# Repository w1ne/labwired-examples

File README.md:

# LabWired Examples

Real firmware, inspectable circuit diagrams, reproducible simulator oracles, and (when relevant) parametric mechanical models in [KernelCAD](https://kernelcad.com/).

This repository is for runnable hardware verification stories, **not concept art or untested AI-generated designs**. Each example states which behavior was verified, where the simulator approximates hardware, and what remains missing.

## Catalog

| Example | Firmware and electronics | Mechanics | Evidence |
| --- | --- | --- | --- |
| [Game Boy-compatible handheld](examples/gaming/gameboy-handheld/) | STM32F411 C firmware runs Peanut-GB and an original ROM; ILI9341 and eight controls | Shared carrier/case interfaces, attached exact-source KiCad board, 59 CAD parts and 58 fixed mates | Saved-project MCU verification, host ROM behavior, browser input, hosted native PCB DRC/attachment and static CAD checks; no physical hardware |
| [HeyPCB imported-board acceptance sample](examples/pcb/heypcb-import-acceptance/) | Seven pinned KiCad PCB files and model-gap evidence; no full-board pass | No mechanical model | Source blobs verified; seven imports reported in unmerged PR #2934; none completely simulated |
| [Industrial BLDC fault verification](examples/industrial/bldc-fault-verification/) | STM32L476 compiled C, 24 V motor plant, three digital fault flags, inverter shutdown | No mechanical model in this example | Normal spin-up and 3 fault scenarios model-verified; ideal MCU supply, no physical bench |
| [Quadrotor co-design](examples/robotics/quadrotor-bldc/) | Four STM32L476 C channels; separate native six-layer ESC with zero configured ERC/DRC findings | 38-part saved KernelCAD revision 5 with populated native ESC and FC; four rotor joints | Candidate browser: 360 exact motor/CAD observations, isolated fault, pause and reset. Actual board simulation and flight remain open. |

## Featured video

[Watch the 75-second quadrotor co-design engineering preview](examples/robotics/quadrotor-bldc/media/quadrotor-engineering-preview.mp4): editable CAD, exploded assembly, native schematic/PCB, four live motor channels, a selected-channel fault, pause and reset. This is actual application footage of a candidate STM32 propulsion bench. The physical OpenESC board and aircraft flight are not simulated by that bench.

## Run

Open an example directory. It contains firmware source, the exact LabWired circuit JSON, observed test evidence, editable KernelCAD source when appropriate, and screenshots recorded from the actual tools. Each example links to a runnable LabWired project and a versioned KernelCAD design.

For an introduction to firmware-aware circuit simulation, use the [LabWired circuit simulator guide](https://labwired.com/circuit-simulator/). It links to a GPIO-to-RC oscilloscope demonstration and explains the different browser linear-circuit and native ngspice capabilities. The quadrotor example above is a separate motor-control verification.

## Contribution standard

New examples need catalog-validated connectivity, compilable firmware, an explicit test oracle, and precise model limits. For mechanical projects, keep editable KernelCAD source and verified joints. See [CONTRIBUTING.md](CONTRIBUTING.md).

**Core simulator and firmware-model changes belong in [w1ne/labwired-core](https://github.com/w1ne/labwired-core).** This repository stores reproducible consumers of that engine, not copies of the engine.

## Licensing

Example source and scripts are MIT licensed. Individual CAD assets may carry CC0-1.0 declarations in their metadata. Manufacturer names (including ODrive) are descriptive and do not imply endorsement, compatibility or use of proprietary software.

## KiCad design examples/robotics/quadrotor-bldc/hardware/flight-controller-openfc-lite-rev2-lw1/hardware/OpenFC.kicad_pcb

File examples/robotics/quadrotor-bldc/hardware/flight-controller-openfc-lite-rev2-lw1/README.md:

# OpenFC-Lite revision 2-LW1 — review candidate

This is an editable, separately versioned repair of the pinned OpenFC-Lite
revision 2. It is **not a manufacturing release or a native firmware acceptance**.
The original submodule remains unchanged at
`def4ab29a5af430551aa15756b747e9ad6d4c480`.

The candidate passes the configured KiCad 10.0.8 physical DRC with **zero
errors and zero unconnected items**. One original physical omission remains:
Card1 DAT1 pad 8 has no PCB copper. Its parity warning is retained. ERC has
zero active errors after one exact, source-backed exclusion for the unused
LP5912 PG pin connected to ground. All design rules and ERC severities are
unchanged.

[Editable PCB](hardware/OpenFC.kicad_pcb) ·
[Editable schematic](hardware/OpenFC.kicad_sch) ·
[Seven-sheet review PDF](validation/schematic-rev2-lw1.pdf) ·
[Immutable source and result manifest](source-and-validation.json)

## Changes

| Item | Change and reason | Preserved contract |
| --- | --- | --- |
| U9 BMI270 | Disconnect ASDx/ASCx, physical pads 2/3, from GND in the schematic and PCB. Remove the single GND via that touched both pads and refill the zones. | The two existing copper pads remain; all other physical net assignments are unchanged. |
| U10 SN74LVC1G3157DTBR | Use the separately named TI DTB0006A Rev C land-pattern example, extracted from TI's mask and paste vectors. Reroute the six local connections and move C38 by 0.30 mm to accommodate that geometry. | Body pose, physical pin identities, source 3D model, existing net names, minimum clearance and via rules remain. |
| Original hole-clearance errors | Move J15, J28 and J54 by the recorded small offsets and update their same-net leads. | Pad shapes, contact identities and board outline remain. |
| Four omitted pads | Restore USB1 A8/B8 and LP5912 U7/U15 pad 2 from their existing footprint-library templates. Move one GND via by 0.1393 mm to clear USB1 A8. | The new pads are isolated NC contacts. No signal or supply is added. |
| Pin and part annotations | Correct U2 GPIO11 to bidirectional, U15 OUT to power output, U7 physical PG3/GND5 identity, Q1/Q2 manufacturer to ALLPOWER, and the U15 500 mA heading. Copy missing PCB MPN/manufacturer fields from the original schematic. | No passive component is retyped as a power source. Part numbers and existing connections remain. |
| ERC intent | Add seven PWR_FLAG symbols only at reviewed external entries or regulator/inductor/diode source paths. Add one exact PG-to-GND exclusion with its TI reference. | The importer ignores these annotations as electrical sources. The unpowered circuit still refuses the actual battery-input net. |
| Revision identity | Date all seven copied sheets 2026-11-12 and label them 2-LW1. | Upstream revision 2 remains available unchanged. |

The LP5912 NC restorations use the existing source/KiCad pattern: 0.375 ×
0.4 mm pads at x = ±0.8875 mm. TI's separate example uses different dimensions.
This repair does not claim that the source pattern is TI's land-pattern
example. U10's new footprint is explicitly a TI example extraction and is
recorded separately.

## Manufacturer evidence

Bosch's [BMI270 datasheet BST-BMI270-DS000-08](https://www.bosch-sensortec.com/media/boschsensortec/downloads/datasheets/bst-bmi270-ds000.pdf),
page 135, states for the auxiliary pins: **“Do not connect to GND.”**
The original board assigned both pads to GND and one GND via physically
contacted both. The final read-only KiCad shape test checks each restored
or corrected NC pad against all pads, tracks, vias and filled copper on its
copper layer. All six tested pads have zero contacts.

TI's [SN74LVC1G3157 datasheet SCES424O](https://www.ti.com/lit/ds/symlink/sn74lvc1g3157.pdf),
pages 54–55, provides the DTB0006A example mask and paste geometry used for
U10. The extraction retains the polygon contours, rounded corners, 0.1 mm
primitive stroke, separate paste apertures and 0.01 mm anchors. This provides
a nominal 0.10 mm copper gap against the existing 0.09 mm rule. The footprint
is not approximated by pad rectangles.

TI's [LP5912 datasheet SNVSA77D](https://www.ti.com/lit/ds/symlink/lp5912.pdf),
section 6, identifies PG as pad 3 and GND as pad 5. Section 8.3.6 permits an
unused PG pin to be grounded or left floating. The source connects both
pads to GND. The repaired symbol has the correct identity and open-collector
annotation. KiCad's generic rule still flags that explicitly permitted
connection against the GND PWR_FLAG. Only that marker's two pin UUIDs and
sheet paths are excluded; the reason and PDF hash are stored in the project
and [exclusion receipt](validation/documented-pg-erc-exclusion.json).

PDF hashes, source-library hashes and exact geometry changes are preserved
in the manifest and per-change receipts. These checks do not qualify solder
processes, current capacity, signal integrity, thermal behavior or production
yield.

## Observed checks

| KiCad 10.0.8 check | Pinned source | Revision 2-LW1 |
| --- | ---: | ---: |
| Physical DRC errors | 5: four hole-clearance, one copper-clearance | 0 |
| Physical DRC warnings | 11 | 5 |
| Unconnected PCB items | 0 | 0 |
| Schematic/PCB parity warnings | 17 | 1: Card1 DAT1 pad 8 omitted |
| Active ERC errors | 9: eight supply declarations, one input-driver declaration | 0 |
| ERC warnings | 182 | 178 |
| Exact documented ERC exclusions | 0 | 1: unused U7 PG3 grounded |

The five final physical warnings are four preserved source/library footprint
mismatches and the original non-mirrored `B = SIGNAL` annotation outside the
board. The 178 ERC warnings are retained; this repair does not reclassify
unknown pin roles or change the global pin-compatibility matrix to clear them.
The installed environment substitutes DejaVu for the unavailable Tokyo font.

The final board has **164 footprints and 583 pad objects**, up from 579 pad
objects. Its 19 zones were refilled with the original rules. All 445
schematic electrical endpoints remain. Only U9 pads 2/3 change their net
assignment. The six U10 pads each retain an actual same-net track contact.
See [native PCB proof](validation/final-pcb-connectivity-proof.json) and
[schematic endpoint proof](validation/schematic-connectivity-proof.json).

The actual app importer produces the same 160-part, 82-net graph before and
after the ERC flags and symbol annotations. Diagram, resolved nets, mapping,
compiler result and lowerer result are identical. The source-free import
still fails with `PWR_RAIL_UNDRIVEN` on `net@C22:1`, which contains the real
P1/J29 battery input and U6/U16 input rails. This proves that ERC annotations
cannot create an ideal battery or regulator supply. It does **not** prove a
powered native boot or qualify the RP2354B internal buck regulator.

## Remaining physical omission

Card1 DAT1 pad 8 is present in the schematic as an unused contact and in the
source footprint library, but absent from the native PCB. The exact 0.7 ×
1.6 mm library pad overlaps three existing power vias and approaches a USB
D− via and a GND via. A bounded same-net reroute was tested; it intersected
adjacent USB/DVDD/IOVDD escape routing. Those trial power and signal edits
were completely reverted. The accepted board retains the original omission
and its parity warning. No pad was shrunk and no rule or parity exclusion
was added to conceal it.

The rejected-candidate DRC reports remain in `validation/` as evidence of this
limit. They are **not** the final board reports. A broader connector/power/USB
escape redesign and its signal-integrity review remain required before
calling the copied board complete.

The existing populated KernelCAD revision 4 uses earlier board geometry.
Its fit receipt cannot qualify the moved components or changed copper in
2-LW1. This candidate also does not establish native sensor startup,
Betaflight arming, ESC operation, flight control or physical power-on.

## Model availability at review

The [model inventory](validation/model-resolution-inventory.json) records
107 enabled source model references. Eleven references resolve to ten cached
upstream files; each file matches its exact Git blob at the pinned upstream
commit. The environment lacks 17 standard KiCad STEP files used by 96 other
references. The 57 footprints without models are 53 solder contacts and four
testpoints. The committed hardware refers to the original pinned model
library through relative links; initialize that submodule to resolve them.

All source model paths, offsets and rotations remain unchanged. The native
inductor entries reference generic Murata/Changjiang package models. Their
presence does not establish manufacturer-specific dimensions. Root assembly
work must resolve and inspect the missing models and verify the newly moved
parts before claiming a populated FC fit.

## Reproduce

1. Initialize the original pinned source and its libraries:
   `git submodule update --init --recursive examples/robotics/quadrotor-bldc/hardware/flight-controller-openfc-lite`.
   The two relative library/model links in this copy refer to that source.
2. Use KiCad 10.0.8 with its standard symbol/footprint libraries and the project
   tables. Run `validation/run_native_checks.sh` with an output directory.
   The script does not edit or refill the board; it audits the committed fill.
3. Run the read-only `validation/verify_pcb.py` with KiCad's `pcbnew` Python
   environment, the pinned original board, the copied board, and an output
   receipt path. It compares pad identities, nets, geometry changes and direct
   NC copper contacts, and verifies the single allowed project-metadata delta.
4. To repeat app import checks, set `LABWIRED_APP_ROOT` to the reviewed app
   checkout listed in the manifest. Run `node --import tsx
   validation/audit_import.mjs INPUT.net OUTPUT.json` from that app checkout.
   Compare the recorded before-annotation and final netlists. The exact app
   source and generated metadata are required; an older released catalog
   cannot reproduce this onboarding result.
5. Run the repository's `python3 -m unittest discover -s scripts -p
   'test_*.py' -v` integrity suite. These tests verify archived source/evidence
   consistency; they do not substitute for KiCad or a physical test.

## Source and licence

The copied hardware derives from
[OpenDrone-hw/OpenFC-Lite](https://github.com/OpenDrone-hw/OpenFC-Lite/tree/def4ab29a5af430551aa15756b747e9ad6d4c480).
It remains under the upstream **CERN-OHL-S-2.0** licence, reproduced in
[LICENSE](LICENSE). The enclosing examples repository's general MIT notice
does not replace that hardware licence. This directory is a LabWired repair
candidate, not an upstream release or manufacturer endorsement. The editable
source, explicit changes and verification records accompany the copy.

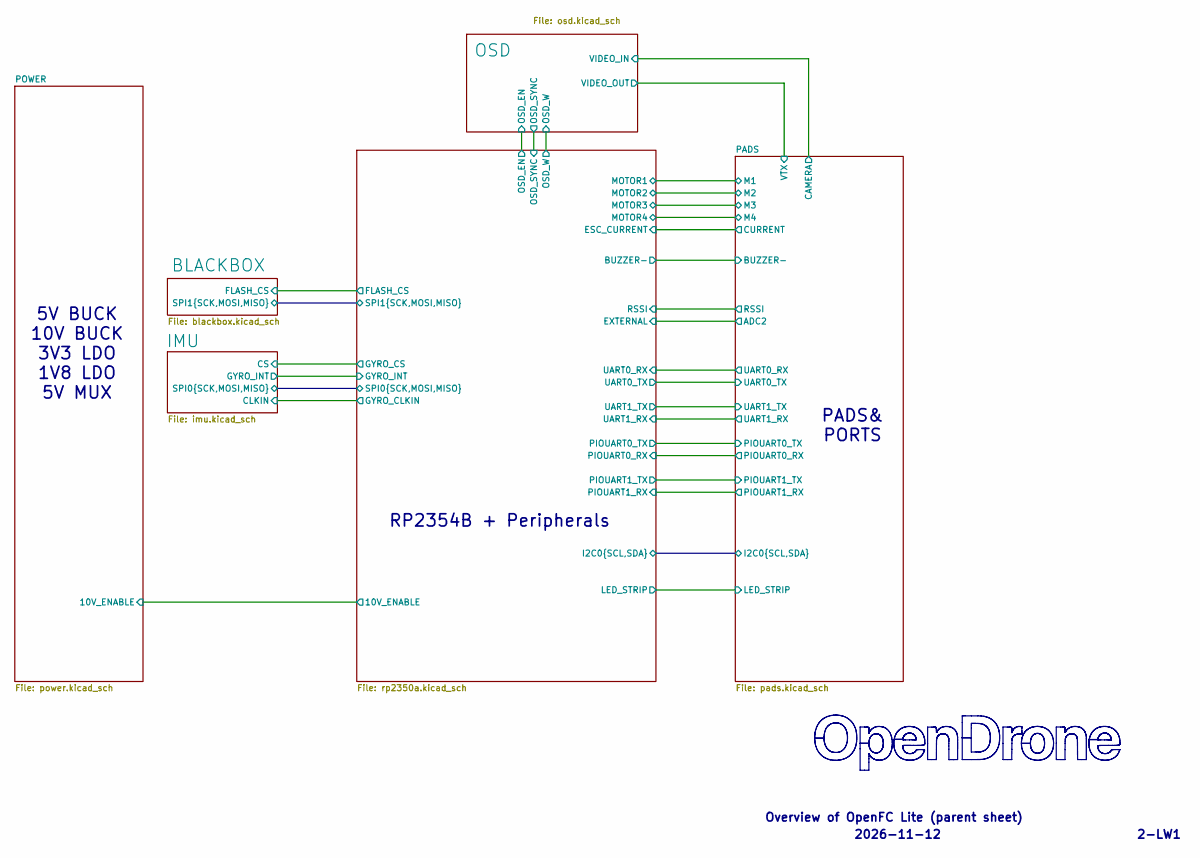
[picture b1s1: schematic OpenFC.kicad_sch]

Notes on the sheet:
Overview of OpenFC Lite (parent sheet)
5V BUCK 10V BUCK 3V3 LDO 1V8 LDO 5V MUX
2-LW1
2026-11-12
RP2354B + Peripherals
PADS& PORTS

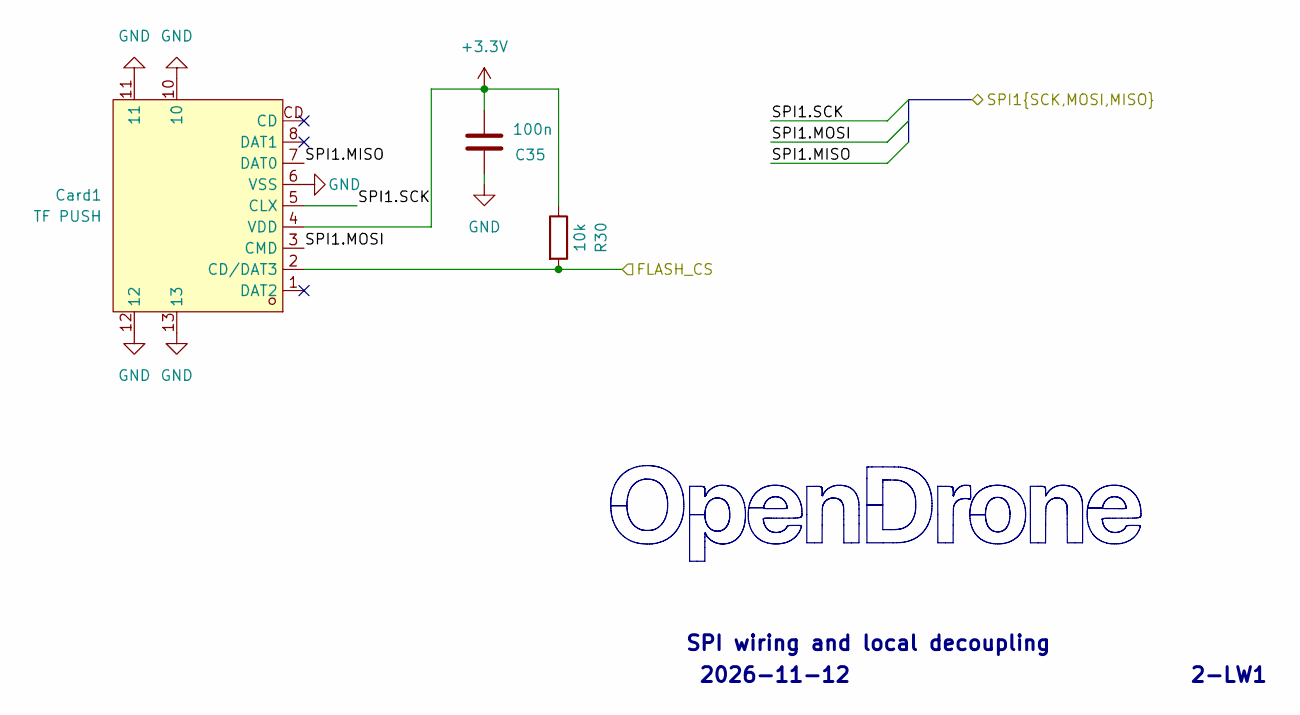
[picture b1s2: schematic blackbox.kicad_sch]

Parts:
C35: 100n; C_0201_0603Metric; MPN GRM033R61E104KE14D; LCSC C76939
Card1: TF PUSH; TF-SMD_TF-PUSH; MPN TF PUSH; LCSC C393941
R30: 10k; R_0201_0603Metric; MPN RC0201FR-0710KL; LCSC C106225

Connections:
+3.3V: C35.1, Card1.4 (VDD), R30.1; also elsewhere on the board
/BLACKBOX/FLASH_CS: Card1.2 (CD/DAT3), R30.2; also elsewhere on the board
/BLACKBOX/SPI1.MISO: Card1.7 (DAT0); also elsewhere on the board
/BLACKBOX/SPI1.MOSI: Card1.3 (CMD); also elsewhere on the board
/BLACKBOX/SPI1.SCK: Card1.5 (CLX); also elsewhere on the board
GND: C35.2, Card1.6 (VSS), Card1.10, Card1.11, Card1.12, Card1.13; also elsewhere on the board

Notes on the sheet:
SPI wiring and local decoupling
2026-11-12
2-LW1

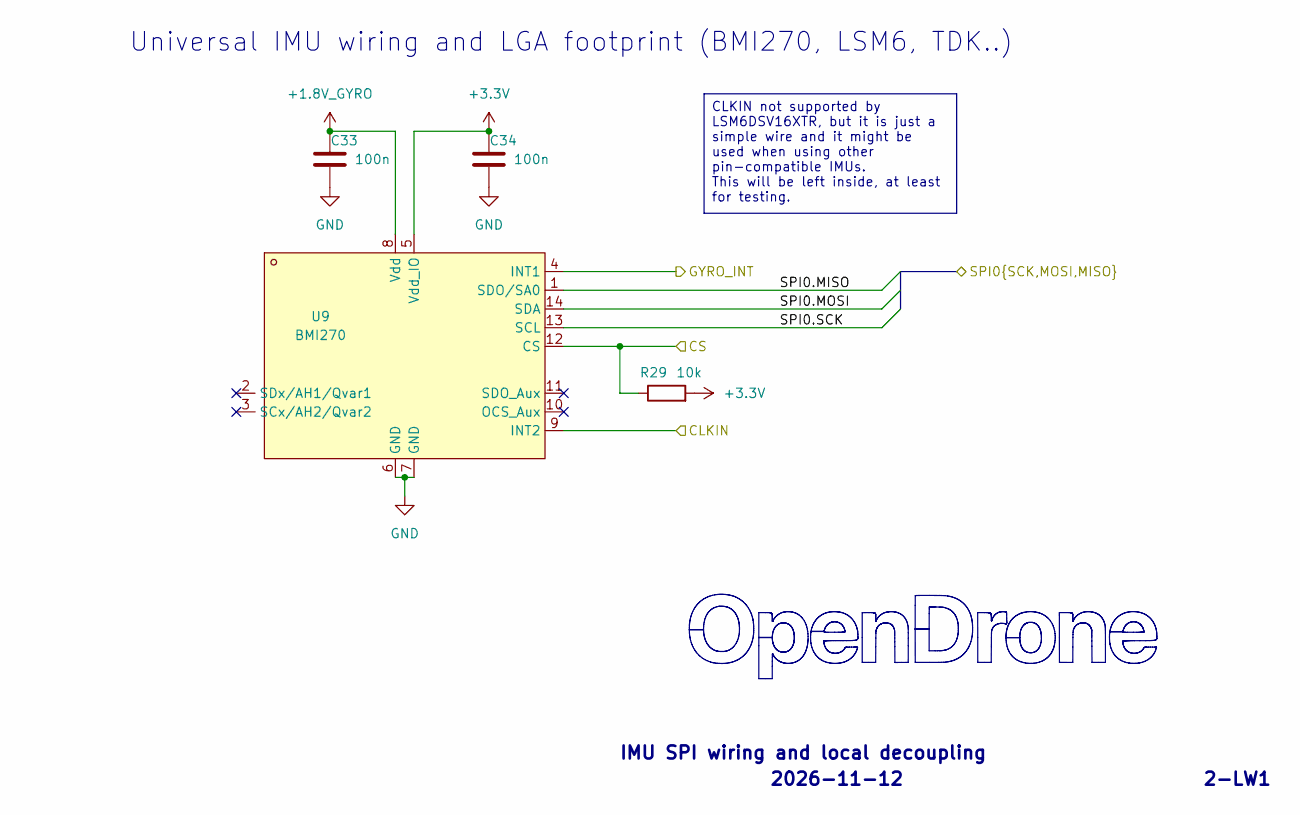
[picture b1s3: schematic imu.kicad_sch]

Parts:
C33, C34: 100n; C_0201_0603Metric; MPN GRM033R61E104KE14D; LCSC C76939
R29: 10k; R_0201_0603Metric; MPN RC0201FR-0710KL; LCSC C106225
U9: BMI270; LGA-14_L3.0-W2.5-P0.50-BR; MPN BMI270; LCSC C2836813

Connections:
+1.8V_GYRO: C33.1, U9.8 (Vdd); also elsewhere on the board
+3.3V: C34.1, R29.2, U9.5 (Vdd_IO); also elsewhere on the board
/IMU/CLKIN: U9.9 (INT2); also elsewhere on the board
/IMU/CS: R29.1, U9.12 (CS); also elsewhere on the board
/IMU/GYRO_INT: U9.4 (INT1); also elsewhere on the board
/IMU/SPI0.MISO: U9.1 (SDO/SA0); also elsewhere on the board
/IMU/SPI0.MOSI: U9.14 (SDA); also elsewhere on the board
/IMU/SPI0.SCK: U9.13 (SCL); also elsewhere on the board
GND: C33.2, C34.2, U9.6 (GND), U9.7 (GND); also elsewhere on the board

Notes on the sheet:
2-LW1
2026-11-12
IMU SPI wiring and local decoupling
Universal IMU wiring and LGA footprint (BMI270, LSM6, TDK..)
CLKIN not supported by LSM6DSV16XTR, but it is just a simple wire and it might be used when using other pin-compatible IMUs. This will be left inside, at least for testing.

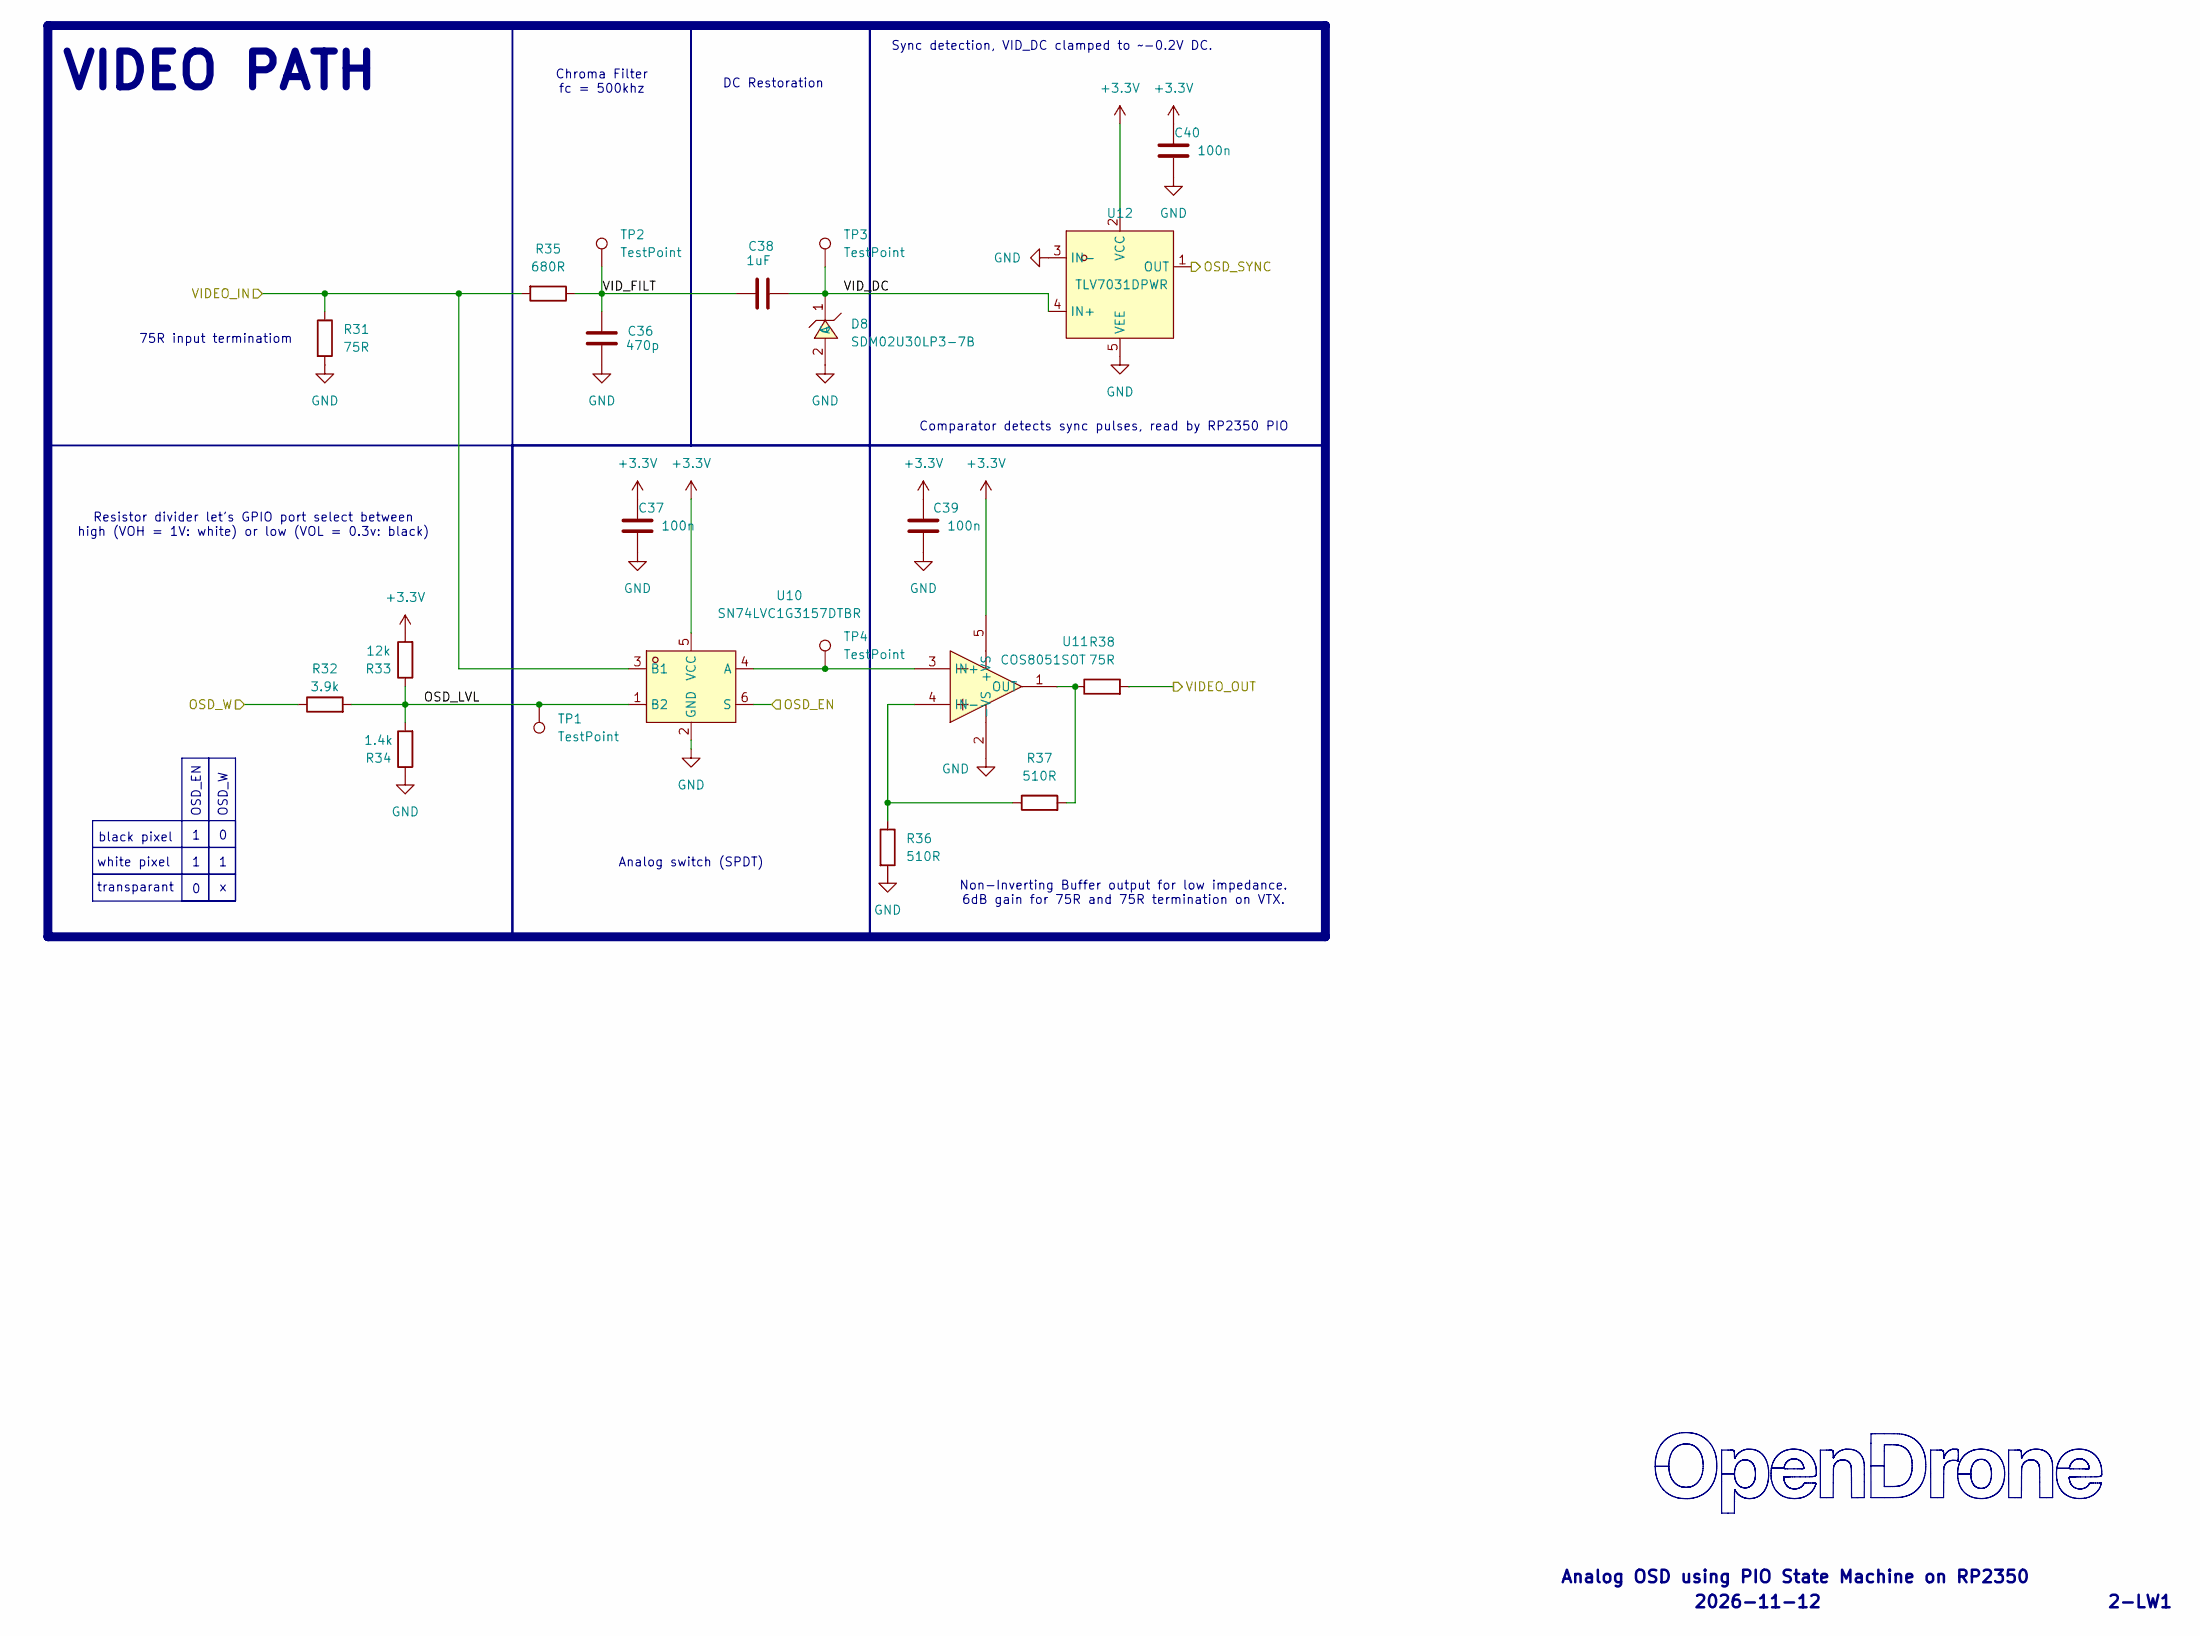
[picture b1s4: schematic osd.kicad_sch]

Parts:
C36: 470p; C_0201_0603Metric; MPN CC0201JRX7R9BB471; LCSC C526944
C37, C39, C40: 100n; C_0201_0603Metric; MPN GRM033R60J104KE19D; LCSC C76928
C38: 1uF; C_0402_1005Metric; MPN CL05A105KA5NQNC; LCSC C52923
D8: SDM02U30LP3-7B; X3-DFN0603-2_L0.6-W0.3-RD; MPN SDM02U30LP3-7B; LCSC C151629
R31, R38: 75R; R_0201_0603Metric; MPN RC0201FR-0775RL; LCSC C274878
R32: 3.9k; R_0201_0603Metric; MPN RC0201FR-073K9L; LCSC C273280
R33: 12k; R_0201_0603Metric; MPN 0201WMF1202TEE; LCSC C270363
R34: 1.4k; R_0201_0603Metric; MPN 0201WMF1401TEE; LCSC C423739
R35: 680R; R_0201_0603Metric; MPN 0201WMF6800TEE; LCSC C473509
R36, R37: 510R; R_0201_0603Metric; MPN RC0201FR-07510RL; LCSC C57784
TP1, TP2, TP3, TP4: TestPoint; TestPoint_Pad_D1.5mm
U10: SN74LVC1G3157DTBR; TI_DTB0006A_RevC_SMD; MPN SN74LVC1G3157DTBR; LCSC C2673087
U11: COS8051SOT; SOT-23-5_L3.0-W1.7-P0.95-LS2.8-BR; MPN COS8051SOT; LCSC C7463385
U12: TLV7031DPWR; X2SON-4_L0.8-W0.8-P0.48-TL-A; MPN TLV7031DPWR; LCSC C2876045

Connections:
+3.3V: C37.1, C39.1, C40.1, R33.2, U10.5 (VCC), U11.5 (+VS), U12.2 (VCC); also elsewhere on the board
/OSD/OSD_EN: U10.6 (S); also elsewhere on the board
/OSD/OSD_LVL: R32.2, R33.1, R34.2, TP1.1 (1_1), U10.1 (B2)
/OSD/OSD_SYNC: U12.1 (OUT); also elsewhere on the board
/OSD/OSD_W: R32.1; also elsewhere on the board
/OSD/VIDEO_IN: R31.1, R35.2, U10.3 (B1); also elsewhere on the board
/OSD/VIDEO_OUT: R38.2; also elsewhere on the board
/OSD/VID_DC: C38.2, D8.1 (C), TP3.1 (1_1), U12.4 (IN+)
/OSD/VID_FILT: C36.1, C38.1, R35.1, TP2.1 (1_1)
GND: C36.2, C37.2, C39.2, C40.2, D8.2 (A), R31.2, R34.1, R36.2, U10.2 (GND), U11.2 (-VS), U12.3 (IN-), U12.5 (VEE); also elsewhere on the board
unnamed: TP4.1 (1_1), U10.4 (A), U11.3 (IN+)
unnamed: R36.1, R37.1, U11.4 (IN-)
unnamed: R37.2, R38.1, U11.1 (OUT)

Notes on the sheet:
black pixel
Comparator detects sync pulses, read by RP2350 PIO
2026-11-12
Analog OSD using PIO State Machine on RP2350
Sync detection, VID_DC clamped to ~-0.2V DC.
Non-Inverting Buffer output for low impedance. 6dB gain for 75R and 75R termination on VTX.
2-LW1
white pixel
75R input terminatiom
OSD_W
Chroma Filter fc = 500khz
VIDEO PATH
Analog switch (SPDT)
OSD_EN
transparant
DC Restoration
Resistor divider let's GPIO port select between high (VOH = 1V: white) or low (VOL = 0.3v: black)

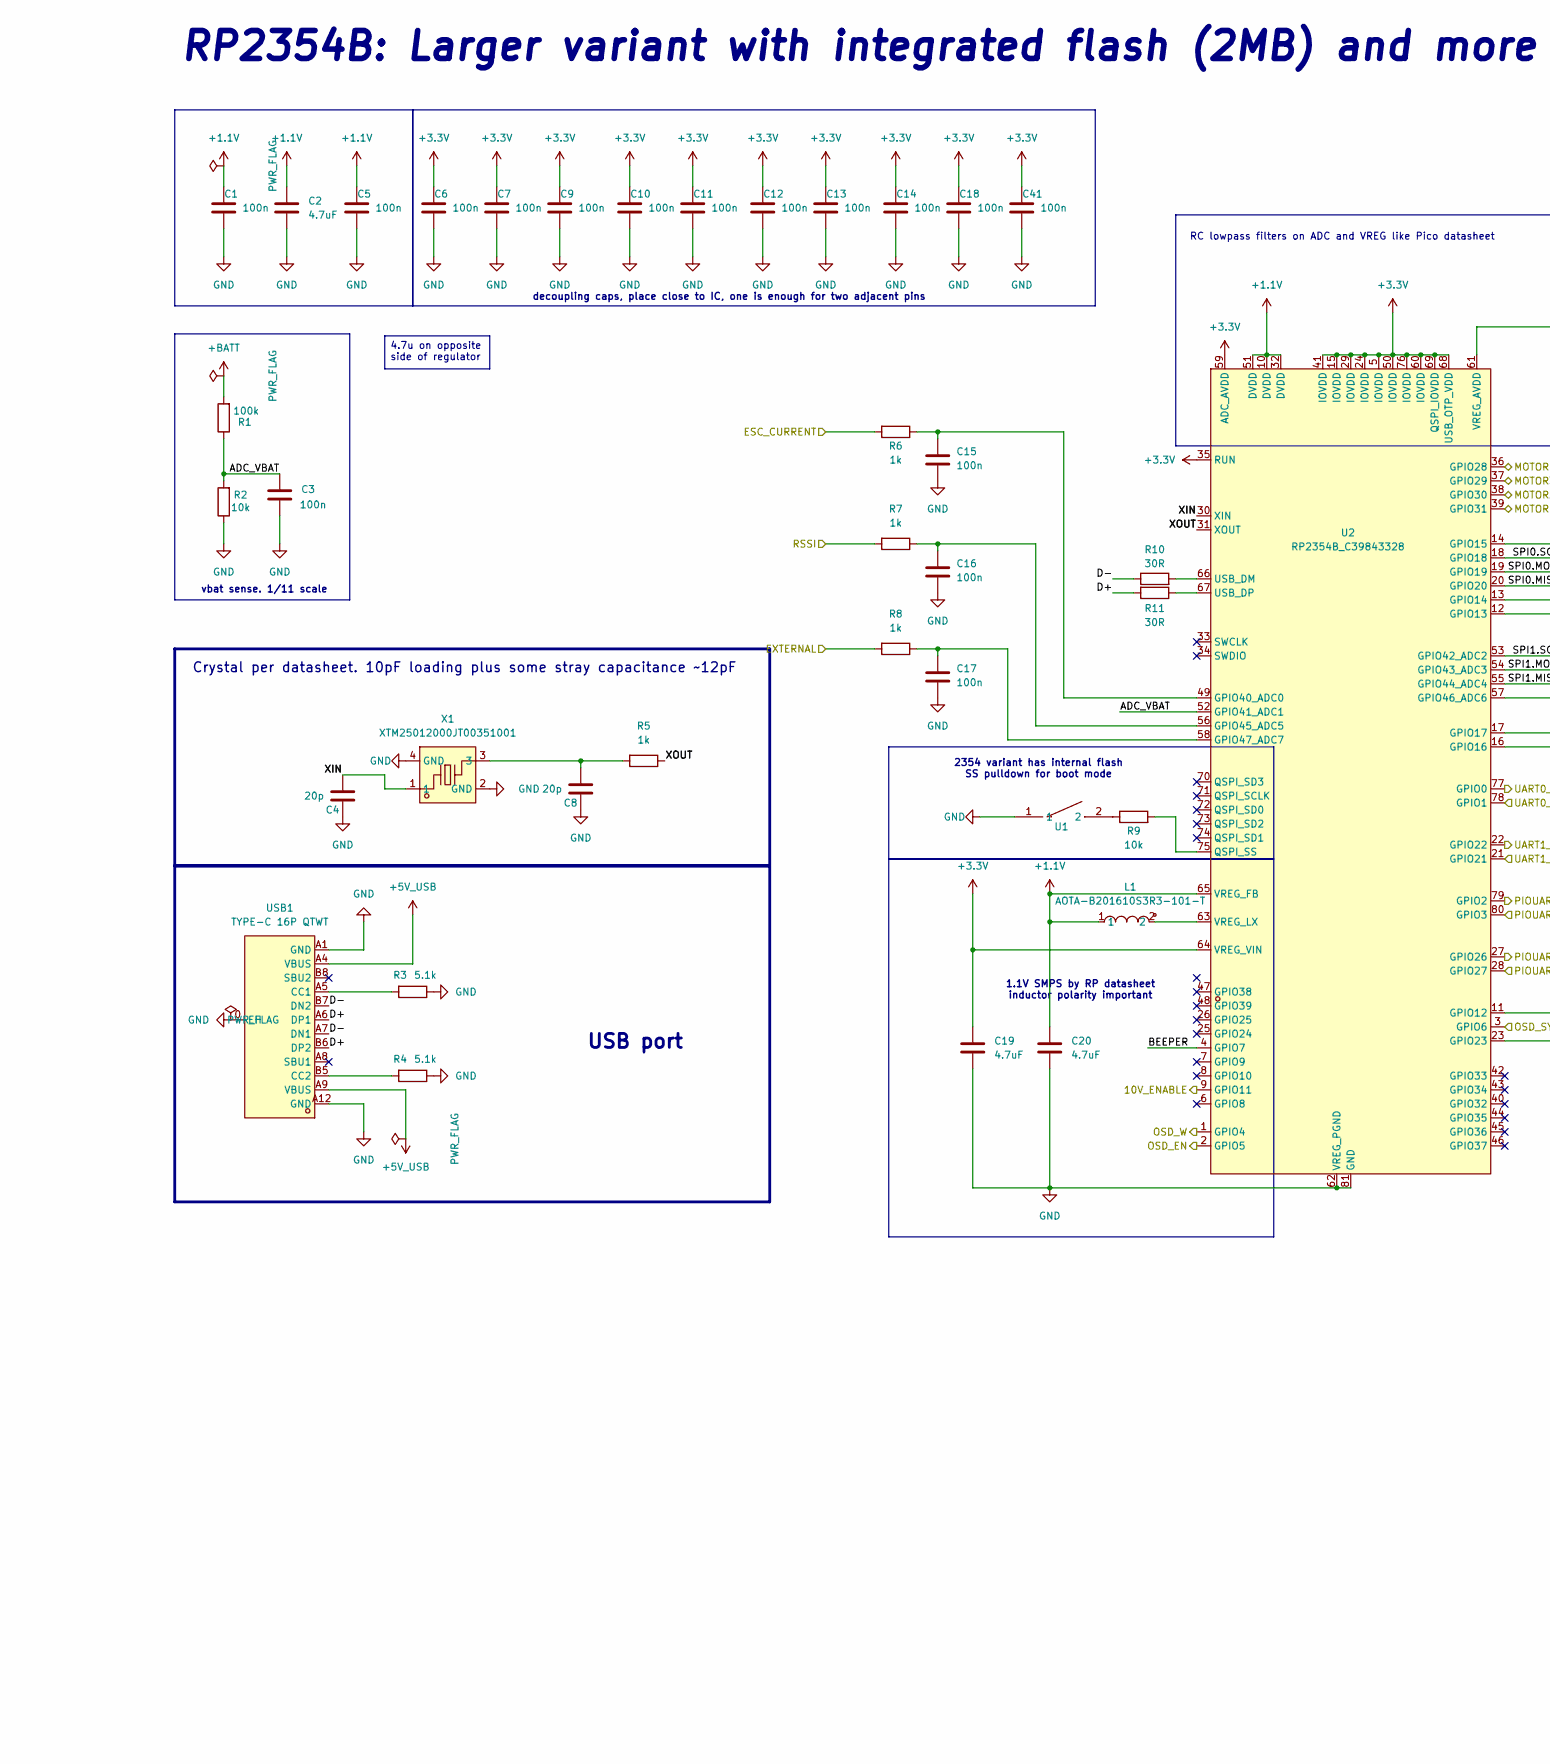
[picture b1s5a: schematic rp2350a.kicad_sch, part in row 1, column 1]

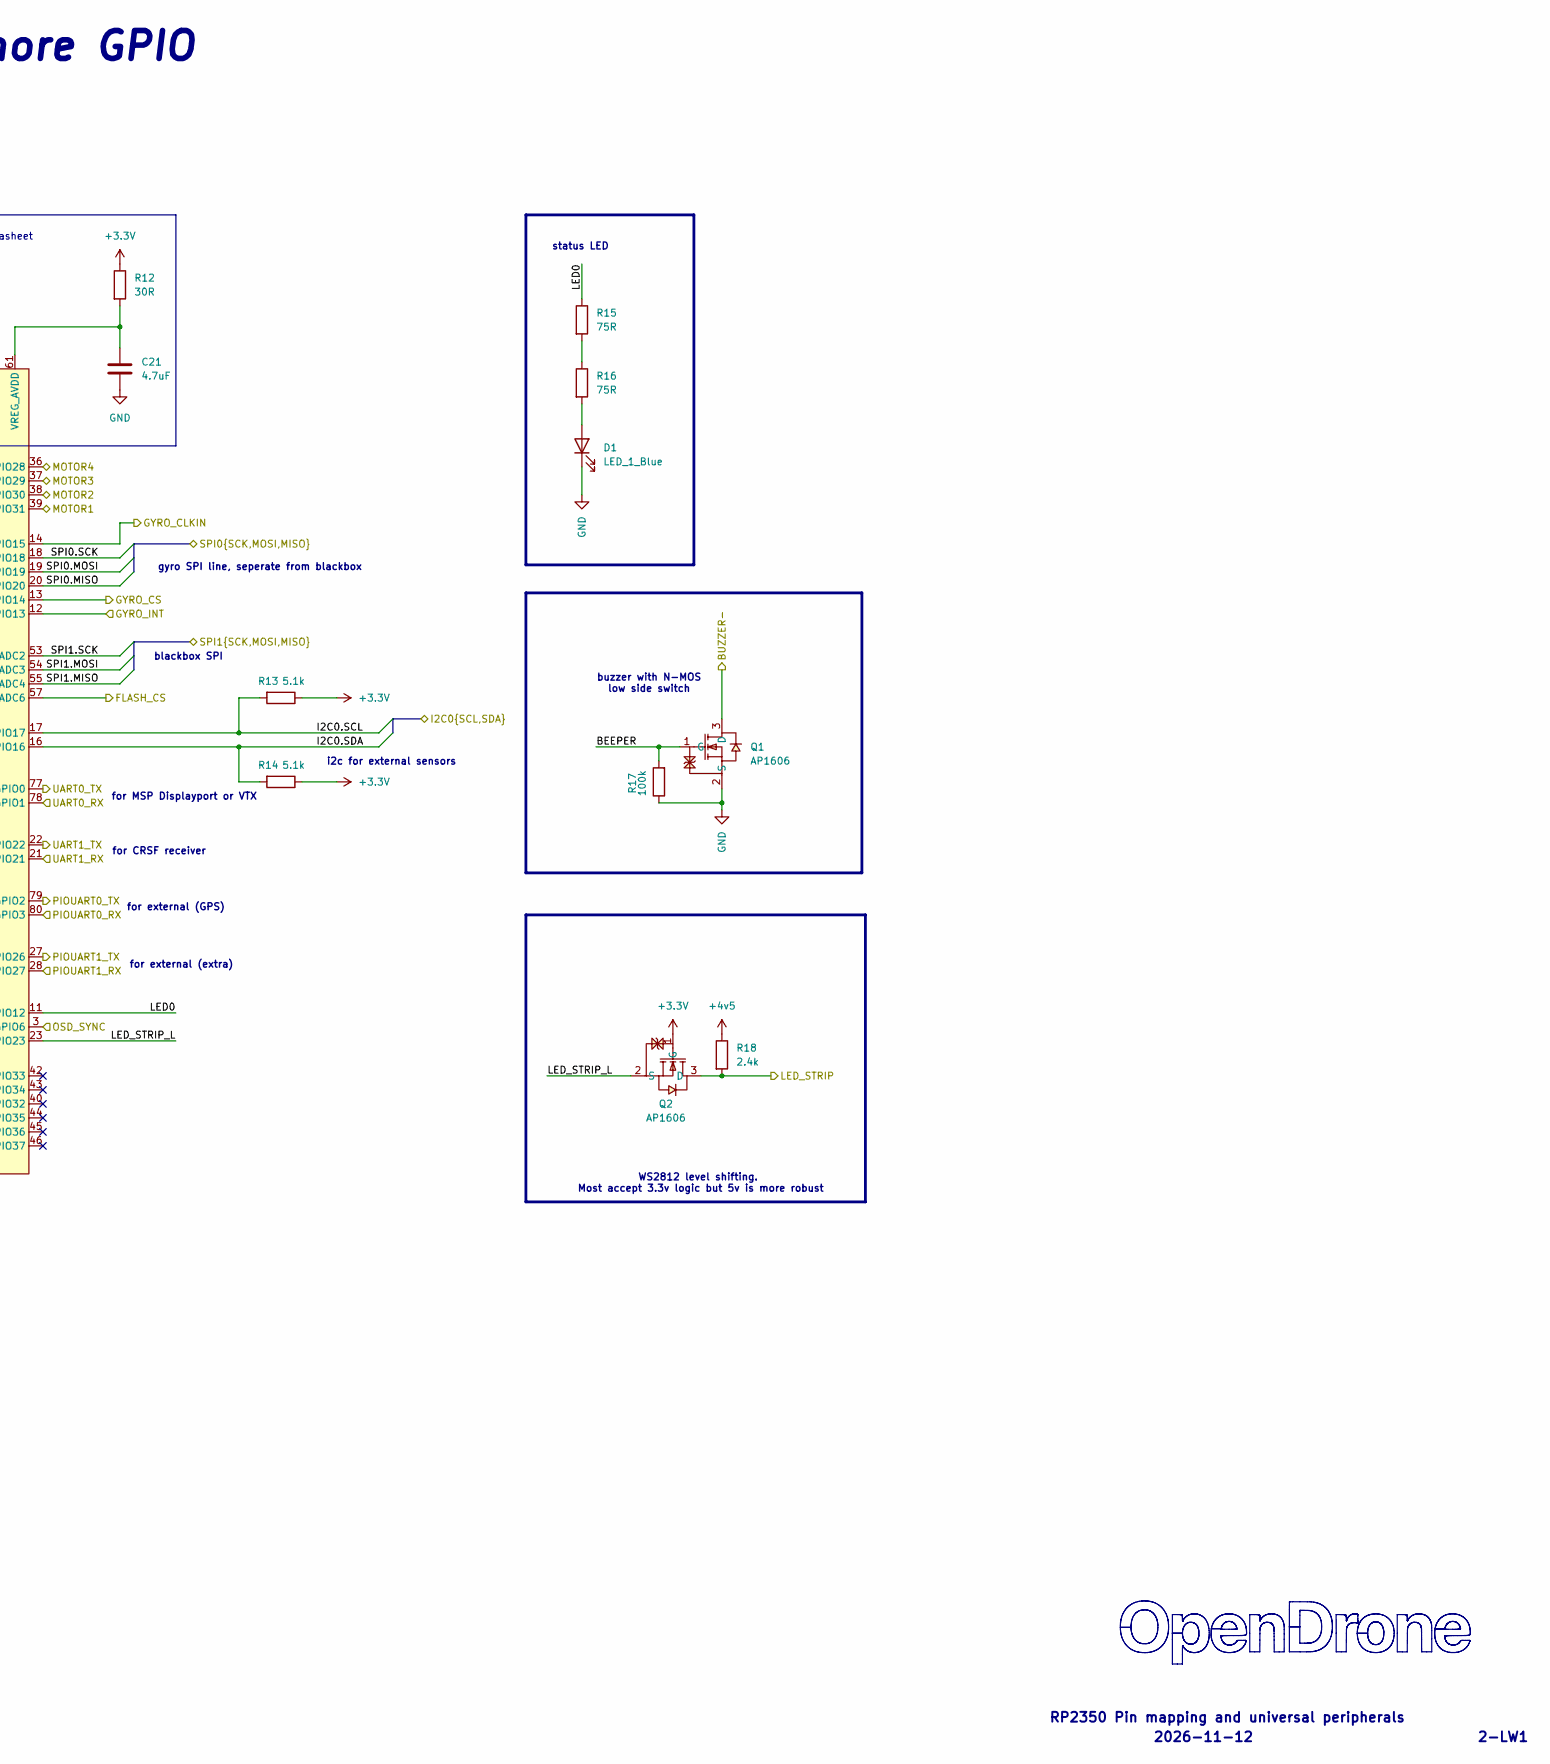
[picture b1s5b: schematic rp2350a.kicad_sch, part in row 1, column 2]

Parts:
C1, C3, C5, C6, C7, C9, C10, C11, C12, C13, C14, C15, C16, C17, C18, C41: 100n; C_0201_0603Metric; MPN GRM033R61E104KE14D; LCSC C76939
C2, C19, C20, C21: 4.7uF; C_0402_1005Metric; MPN CL05A475MP5NRNC; LCSC C23733
C4, C8: 20p; C_0201_0603Metric; MPN GRM0335C1H200JA01D; LCSC C76923
D1: LED_1_Blue; LED_0402_1005Metric; MPN XL-1005UBC; LCSC C22355736
L1: AOTA-B201610S3R3-101-T; IND-SMD_L2.0-W1.6_AOTA-B201610S3R3-101-T; MPN AOTA-B201610S3R3-101-T; LCSC C42411119
Q1, Q2: AP1606; DFN-3L_L1.0-W0.6-P0.65-BR; MPN AP1606; LCSC C2849580
R1, R17: 100k; R_0201_0603Metric; MPN 0201WMF1003TEE; LCSC C270364
R2, R9: 10k; R_0201_0603Metric; MPN RC0201FR-0710KL; LCSC C106225
R3, R4, R13, R14: 5.1k; R_0201_0603Metric; MPN 0201WMF5101TEE; LCSC C270344
R5, R6, R7, R8: 1k; R_0201_0603Metric; MPN 0201WMF1001TEE; LCSC C270365
R10, R11, R12: 30R; R_0201_0603Metric; MPN NQ01WMJ0300TEE; LCSC C778391
R15, R16: 75R; R_0201_0603Metric; MPN RC0201FR-0775RL; LCSC C274878
R18: 2.4k; R_0201_0603Metric; MPN RTT012401FTH; LCSC C166281
U1: TS2306A 240GF MSM 9_C2976675; SW-SMD_4P-L3.0-W2.0-P0.85-LS3.5; MPN TS2306A 240gf MSM 9; LCSC C2976675
U2: RP2354B_C39843328; QFN-80_L10.0-W10.0-P0.40-TL-EP3.4; MPN RP2354B; LCSC C39843328
USB1: TYPE-C 16P QTWT; USB-TYPE-C-SMD_TYPE-C-16P-QTWT; MPN TYPE-C 16P QTWT; LCSC C5187472
X1: XTM25012000JT00351001; CRYSTAL-SMD_4P-L2.5-W2.0-BL-A; MPN XTM25012000JT00351001; LCSC C37635340

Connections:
+1.1V: C1.1, C2.1, C5.1, C20.1, L1.1, U2.10 (DVDD), U2.32 (DVDD), U2.51 (DVDD), U2.65 (VREG_FB)
+3.3V: C6.1, C7.1, C9.1, C10.1, C11.1, C12.1, C13.1, C14.1, C18.1, C19.1, C41.1, Q2.1 (G), R12.1, R13.1, R14.1, U2.5 (IOVDD), U2.15 (IOVDD), U2.24 (IOVDD), U2.29 (IOVDD), U2.35 (RUN), U2.41 (IOVDD), U2.50 (IOVDD), U2.59 (ADC_AVDD), U2.60 (IOVDD), U2.64 (VREG_VIN), U2.68 (USB_OTP_VDD), U2.69 (QSPI_IOVDD), U2.76 (IOVDD); also elsewhere on the board
+4v5: R18.1; also elsewhere on the board
+5V_USB: USB1.A4 (VBUS), USB1.A9 (VBUS); also elsewhere on the board
+BATT: R1.2; also elsewhere on the board
/BLACKBOX/FLASH_CS: U2.57 (GPIO46_ADC6); also elsewhere on the board
/BLACKBOX/SPI1.MISO: U2.55 (GPIO44_ADC4); also elsewhere on the board
/BLACKBOX/SPI1.MOSI: U2.54 (GPIO43_ADC3); also elsewhere on the board
/BLACKBOX/SPI1.SCK: U2.53 (GPIO42_ADC2); also elsewhere on the board
/IMU/CLKIN: U2.14 (GPIO15); also elsewhere on the board
/IMU/CS: U2.13 (GPIO14); also elsewhere on the board
/IMU/GYRO_INT: U2.12 (GPIO13); also elsewhere on the board
/IMU/SPI0.MISO: U2.20 (GPIO20); also elsewhere on the board
/IMU/SPI0.MOSI: U2.19 (GPIO19); also elsewhere on the board
/IMU/SPI0.SCK: U2.18 (GPIO18); also elsewhere on the board
/OSD/OSD_EN: U2.2 (GPIO5); also elsewhere on the board
/OSD/OSD_SYNC: U2.3 (GPIO6); also elsewhere on the board
/OSD/OSD_W: U2.1 (GPIO4); also elsewhere on the board
/PADS/ADC2: R8.2; also elsewhere on the board
/PADS/BUZZER-: Q1.3 (D); also elsewhere on the board
/PADS/CURRENT: R6.2; also elsewhere on the board
/PADS/I2C0.SCL: R13.2, U2.17 (GPIO17); also elsewhere on the board
/PADS/I2C0.SDA: R14.2, U2.16 (GPIO16); also elsewhere on the board
/PADS/LED_STRIP: Q2.3 (D), R18.2; also elsewhere on the board
/PADS/M1: U2.39 (GPIO31); also elsewhere on the board
/PADS/M2: U2.38 (GPIO30); also elsewhere on the board
/PADS/M3: U2.37 (GPIO29); also elsewhere on the board
/PADS/M4: U2.36 (GPIO28); also elsewhere on the board
/PADS/PIOUART0_RX: U2.80 (GPIO3); also elsewhere on the board
/PADS/PIOUART0_TX: U2.79 (GPIO2); also elsewhere on the board
/PADS/PU1RX: U2.28 (GPIO27); also elsewhere on the board
/PADS/PU1TX: U2.27 (GPIO26); also elsewhere on the board
/PADS/RSSI: R7.2; also elsewhere on the board
/PADS/U1RX: U2.21 (GPIO21); also elsewhere on the board
/PADS/UART0_RX: U2.78 (GPIO1); also elsewhere on the board
/PADS/UART0_TX: U2.77 (GPIO0); also elsewhere on the board
/PADS/UART1_TX: U2.22 (GPIO22); also elsewhere on the board
/POWER/10V_ENABLE: U2.9 (GPIO11); also elsewhere on the board
/RP2350A/ADC_VBAT: C3.2, R1.1, R2.2, U2.52 (GPIO41_ADC1)
/RP2350A/BEEPER: Q1.1 (G), R17.2, U2.4 (GPIO7)
/RP2350A/D+: R11.2, USB1.A6 (DP1), USB1.B6 (DP2)
/RP2350A/D-: R10.1, USB1.A7 (DN1), USB1.B7 (DN2)
/RP2350A/LED0: R15.1, U2.11 (GPIO12)
/RP2350A/LED_STRIP_L: Q2.2 (S), U2.23 (GPIO23)
/RP2350A/XIN: C4.2, U2.30 (XIN), X1.1
/RP2350A/XOUT: R5.1, U2.31 (XOUT)
GND: C1.2, C2.2, C3.1, C4.1, C5.2, C6.2, C7.2, C8.1, C9.2, C10.2, C11.2, C12.2, C13.2, C14.2, C15.2, C16.2, C17.2, C18.2, C19.2, C20.2, C21.2, C41.2, D1.1 (K), Q1.2 (S), R2.1, R3.1, R4.1, R17.1, U1.1, U2.62 (VREG_PGND), U2.81 (GND), USB1.0 (EH), USB1.A1 (GND), USB1.A12 (GND), X1.2 (GND), X1.4 (GND); also elsewhere on the board
unnamed: C8.2, R5.2, X1.3
unnamed: D1.2 (A), R16.2
unnamed: R9.1, U1.2
unnamed: R15.2, R16.1
unnamed: C15.1, R6.1, U2.49 (GPIO40_ADC0)
unnamed: C16.1, R7.1, U2.56 (GPIO45_ADC5)
unnamed: C17.1, R8.1, U2.58 (GPIO47_ADC7)
unnamed: R9.2, U2.75 (QSPI_SS)
unnamed: R10.2, U2.66 (USB_DM)
unnamed: R11.1, U2.67 (USB_DP)
unnamed: C21.1, R12.2, U2.61 (VREG_AVDD)
unnamed: L1.2, U2.63 (VREG_LX)
unnamed: R3.2, USB1.A5 (CC1)
unnamed: R4.2, USB1.B5 (CC2)

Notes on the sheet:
RP2350 Pin mapping and universal peripherals
vbat sense. 1/11 scale
RP2354B: Larger variant with integrated flash (2MB) and more GPIO
blackbox SPI
2026-11-12
for MSP Displayport or VTX
2354 variant has internal flash SS pulldown for boot mode
for CRSF receiver
gyro SPI line, seperate from blackbox
decoupling caps, place close to IC, one is enough for two adjacent pins
for external (extra)
Crystal per datasheet. 10pF loading plus some stray capacitance ~12pF
for external (GPS)
i2c for external sensors
WS2812 level shifting. Most accept 3.3v logic but 5v is more robust
2-LW1
status LED
RC lowpass filters on ADC and VREG like Pico datasheet
USB port
1.1V SMPS by RP datasheet inductor polarity important
buzzer with N-MOS low side switch
4.7u on opposite side of regulator
